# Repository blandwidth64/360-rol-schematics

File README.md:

# 360-rol-schematics
a collection of some ring of light revisions, scanned and digitized by me

i started the project in feb 2024 as my excuse to finally learn kicad
PLEASE PROOFREAD MY WORK BEFORE USING ANYTHING PLEASE PLEASE PRETTY PLEASE

along the way im doing my best to annotate all the traces i could competently identify, and for some traces im just guessing.

i will upload the work in order of whenever i am finished or whenever i think its good enough to go out.

thanks to drtrinity.

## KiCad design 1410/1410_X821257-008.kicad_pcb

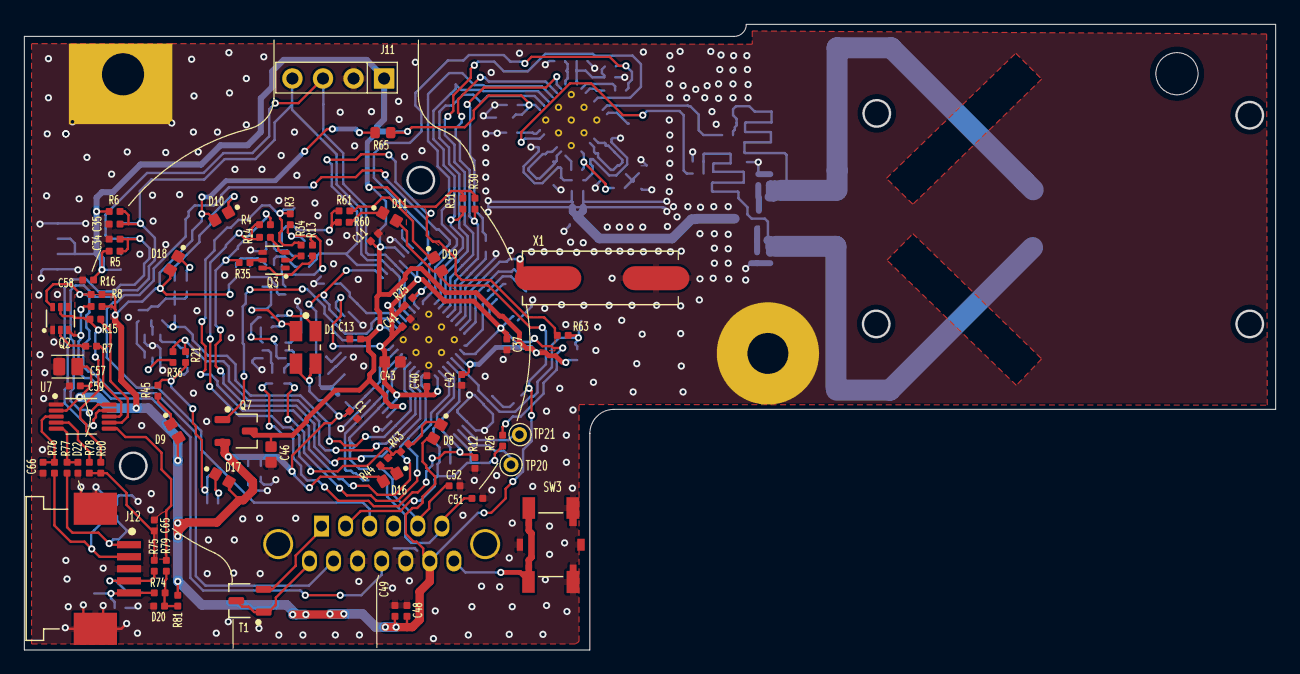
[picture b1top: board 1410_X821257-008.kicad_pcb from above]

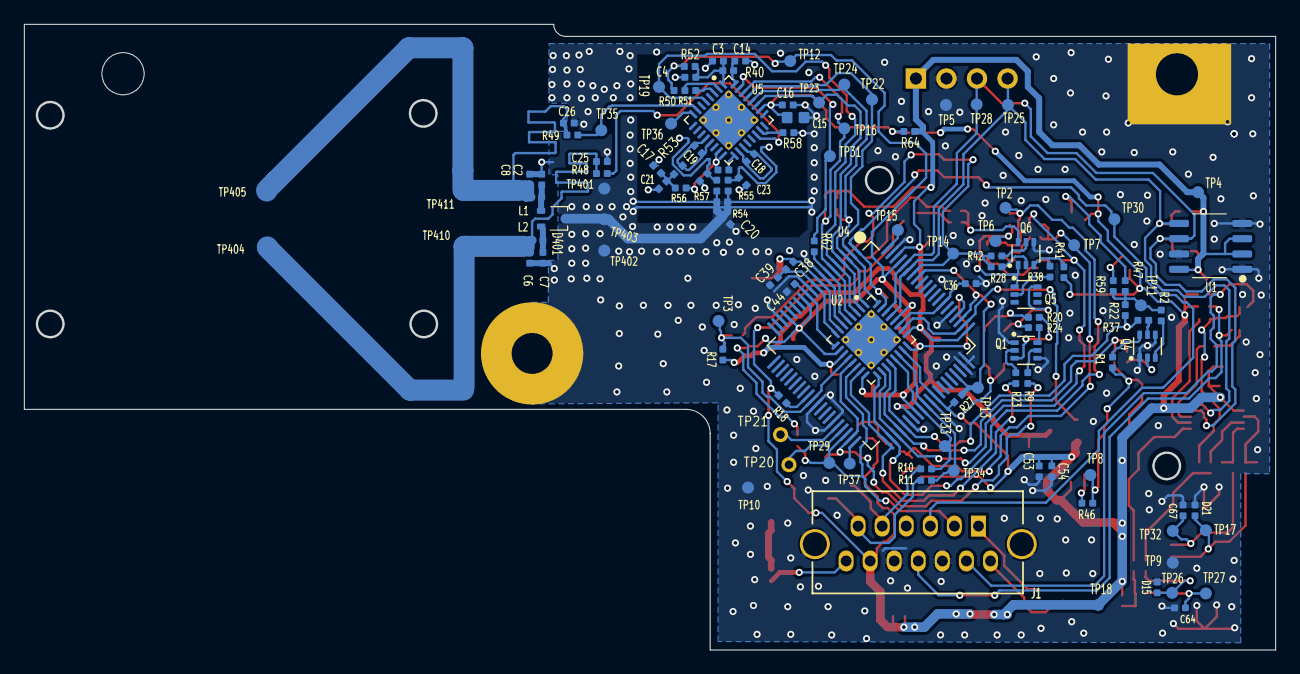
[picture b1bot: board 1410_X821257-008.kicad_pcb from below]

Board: 2 copper layers, 104.0 x 52.0 mm, 192 parts (119 on the bottom side), 64 nets.

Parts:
C1: 1 UF; C_0402_1005Metric
C2, C4, C6, C7, C8, C13, C16, C18, C19, C20, C21, C23, C25, C26, C34, C35, C51, C52, C64, C67: idk; C_0402_1005Metric
C3, C11, C14, C37, C40, C41, C42, C44, C48, C53, C58: 0.1 UF; C_0402_1005Metric
C15: C_0603_1608Metric
C17: 0.022 UF; C_0402_1005Metric
C36: 0.22 UF; C_0402_1005Metric
C38, C39: 27 pF; C_0402_1005Metric
C43, C46: 2.5 UF; C_0603_1608Metric
C49, C54: 2200 PF; C_0402_1005Metric
C57: 10 UF; C_0805_2012Metric
C59: 0.01 UF; C_0402_1005Metric
C65, C66: 62 PF; C_0402_1005Metric
D1: LED_Avago_PLCC4_3.2x2.8mm_CW
D8, D9, D10, D11, D16, D17, D18, D19: LED_0603_1608Metric
D15, D20, D21, D22: D_0402_1005Metric
D401: SOT-523
J1: BORONFPM
J11: PinHeader_1x04_P2.54mm_Vertical
J12: TE_84953-5_1x05-1MP_P1.0mm_Horizontal
L1, L2: L_0402_1005Metric
Q1, Q2, Q3, Q5, Q6: SOT-363_SC-70-6
Q4: NC; SOT-363_SC-70-6
Q7: SOT-23-3
R1, R2, R5, R13, R14, R27, R34, R35, R36, R37, R51, R52, R80, R81: NC; R_0402_1005Metric
R3, R4, R21, R22, R50, R53, R54, R55, R57, R62, R63, R78, R79: 0; R_0402_1005Metric
R6: 1500; R_0402_1005Metric
R7, R8, R15, R16, R25, R26, R40, R42: 10000; R_0402_1005Metric
R9, R17, R23, R28, R30, R31, R38, R41: 1000; R_0402_1005Metric
R10, R11: 22; R_0402_1005Metric
R12: 7.5; R_0402_1005Metric
R18, R56: 47; R_0402_1005Metric
R20: 190; R_0402_1005Metric
R24: 160; R_0402_1005Metric
R43, R44, R45, R46, R47, R59, R60, R61: 30; R_0402_1005Metric
R48, R49: 387; R_0402_1005Metric
R58, R64: 56; R_0402_1005Metric
R65: 2.2; R_0603_1608Metric
R74, R75, R76, R77: 100; R_0402_1005Metric
SW3: SW_Push_1P1T_XKB_TS-1187A
T1: SOT-23-3
TP2, TP3, TP4, TP5, TP6, TP7, TP8, TP9, TP10, TP11, TP12, TP13, TP14, TP15, TP16, TP17, TP18, TP19, TP22, TP23, TP24, TP25, TP26, TP27, TP28, TP29, TP30, TP31, TP32, TP33, TP34, TP35, TP36, TP37, TP401, TP402, TP403, TP404, TP405, TP410, TP411: TestPoint_Pad_D1.0mm
TP20, TP21: TestPoint_THTPad_D1.5mm_Drill0.7mm
U1: ST 24C04RP; SOP-8_3.9x4.9mm_P1.27mm
U2, U5: Microsoft X851186002; LFCSP-32-1EP_5x5mm_P0.5mm_EP3.6x3.6mm_ThermalVias
U4: U4; LQFP-80_12x12mm_P0.5mm
U7: MSOP-10_3x3mm_P0.5mm
UNPOPULATED: NC; R_0402_1005Metric
X1: 12MHz; Crystal_SMD_HC49-SD
unmarkedcap: idk; C_0402_1005Metric

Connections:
ANT_01: C8.1, C26.1, L1.1, R49.1, TP405.1, TP411.1
ANT_01_R1: R49.2, TP35.1, U5.7
ANT_02: C6.2, C25.1, L2.1, R48.1, TP404.1, TP410.1
ANT_02_R1: R48.2, U5.22
BINDSW_N: J1.13, SW3.2
BORONFPMPORT_DN: C52.2, J1.5, R10.2
BORONFPMPORT_DN_R: R10.1, TP33.1, U2.21, U4.49
BORONFPMPORT_DP: C51.2, J1.6, R11.2
BORONFPMPORT_DP_R: R11.1, TP34.1, U2.22, U4.50
BORONFPM_CLK: J1.3, R25.1, TP30.1, U2.31, U4.1
BORONFPM_DATA: J1.2, R26.2, TP29.1, U2.14, U4.38
BORONFPM_DATA_R: C37.1, C40.2, C41.2, C43.2, R25.2, R26.1, R50.1, R52.1, TP12.1, U2.10, U2.16, U2.24, U2.28, U4.13, U4.17, U4.48, U4.64, U4.77
BRD_TEMP_N: J1.7, T1.1, T1.3
BRD_TEMP_P: J1.1, T1.2
CPU_INTERCONN_01: R31.2, TP24.1, U2.1, U4.3, U5.28
CPU_INTERCONN_02: TP23.1, U2.2, U4.4, U5.27
CPU_INTERCONN_03: TP19.1, U2.3, U4.5, U5.5
CPU_INTERCONN_04: R30.2, TP16.1, U2.4, U4.6, U5.30
CPU_INTERCONN_05: R62.1, U2.5, U4.7
CPU_INTERCONN_05_0R: R62.2, TP31.1, U5.31
CPU_INTERCONN_06: TP22.1, U2.32, U4.2, U5.29
EJECTSW_N: J1.10, Q2.3, R8.2
FACEPL_EJECTSW_CIN: R78.1, U7.4
FACEPL_EJECTSW_CIN_0R: C65.2, R75.1, R78.2, R80.2
FACEPL_EJECTSW_CIN_R: D15.1, J12.4, R75.2, TP26.1
FACEPL_EJECTSW_EXC: R79.1, U7.6
FACEPL_EJECTSW_EXC_0R: D20.1, R74.1, R79.2, R81.2
FACEPL_EJECTSW_EXC_R: C64.1, J12.5, R74.2, TP27.1
FACEPL_EJECTSW_TRIG: R15.1, U7.7
FACEPL_PWRSW_CIN: C66.1, R76.1, U7.3
FACEPL_PWRSW_CIN_R: D21.1, J12.2, R76.2, TP17.1
FACEPL_PWRSW_EXC: D22.1, R77.1, U7.5
FACEPL_PWRSW_EXC_R: C67.2, J12.1, R77.2, TP32.1
FACEPL_PWRSW_TRIG: R7.1, U7.8
GND: C1.1, C2.2, C3.1, C4.1, C6.1, C7.1, C8.2, C11.1, C13.2, C14.2, C15.2, C16.2, C17.1, C20.1, C20.2, C21.1, C23.1, C23.2, C25.2, C26.2, C34.2, C35.2, C36.2, C37.2, C39.1, C40.1, C41.1, C42.2, C43.1, C44.1, C46.2, C48.1, C49.1, C51.1, C52.1, C53.1, C54.1, C57.1, C58.2, C59.2, C64.2, C65.1, C66.2, C67.1, D15.2, D20.2, D21.2, D22.2, D401.3, J1.9, J1.11, J1.14, J1.15, J11.2, J12.3, J12.MP, Q1.1, Q1.4, Q2.1, Q2.4, Q3.1, Q3.4, Q4.1, Q4.4, Q6.4, R12.2, R51.2, R54.1, R54.2, R55.1, R55.2, R57.1, R57.2, R58.2, SW3.1, TP5.1, TP9.1, TP10.1, TP401.1, TP402.1, TP403.1, U1.1, U1.4, U1.7, U2.6, U2.33, U4.8, U4.11, U4.18, U4.31, U4.35, U4.46, U4.51, U4.59, U4.60, U4.65, U4.79, U5.3, U5.6, U5.11, U5.14, U5.20, U5.33, U7.1, X1.2, unmarkedcap.1, unmarkedcap.2
I2C_SCL: C34.1, J11.3, R5.1, TP28.1, U1.6, U2.30, U4.76, U7.9
I2C_SDA: C35.1, J11.4, R6.1, TP25.1, U1.5, U2.29, U4.75, U7.10
LED_MAIN_GRN_EN: D1.4, Q5.6, R24.1
LED_MAIN_RED_EN: Q1.3, R20.2
LED_MAIN_RED_EN_R: D1.1, R20.1
LED_PL1_EN: R3.1, R34.1, TP2.1, U2.17, U4.42
LED_PL1_EN_0R: Q5.1, Q6.1, R3.2, R13.1, TP6.1
LED_PL1_EN_R1: D19.1, R61.1
LED_PL1_EN_R2: D11.1, R60.1
LED_PL1_EN_T: Q6.6, R60.2, R61.2
LED_PL2_EN: R4.1, R35.2, U2.18, U4.43
LED_PL2_EN_0R: R4.2, R14.2, R43.2, R44.1, TP7.1
LED_PL2_EN_R1: D8.1, R43.1
LED_PL2_EN_R2: D16.1, R44.2
LED_PL3_EN: R21.1, R36.1, U2.19, U4.44
LED_PL3_EN_0R: R1.1, R21.2, R45.1, R46.1, TP8.1
LED_PL3_EN_R1: D9.1, R45.2
LED_PL3_EN_R2: D17.1, R46.2
LED_PL4_EN: R22.1, R37.1, U2.20, U4.45
LED_PL4_EN_0R: R2.2, R22.2, R47.1, R59.1, TP11.1
LED_PL4_EN_R1: D10.1, R47.2
LED_PL4_EN_R2: D18.1, R59.2
PWRSW_N: J1.8, Q2.6, R16.2
SMD_XTAL: C38.2, U2.7, U4.9, X1.1
SMD_XTAL_C: C38.1, C39.2, U2.8, U4.10
V_2P0: C11.2, C13.1, C42.1, C46.1, C58.1, J11.1, Q7.3, R5.2, R6.2, R17.1, R30.1, R31.1, R64.2, TP4.1, U1.2, U1.3, U1.8, U2.11, U2.25, U4.47, U4.61, U4.78
V_2P7: Q7.1, U2.26, U4.62
V_3P3: C1.2, C48.2, C49.2, C53.2, C54.2, C57.2, C59.1, D1.2, D1.3, D8.2, D9.2, D10.2, D11.2, D16.2, D17.2, D18.2, D19.2, J1.12, Q7.2, R8.1, R16.1, R18.2, R27.2, R41.1, R65.1, R81.1, TP18.1, U2.23, U4.52, U7.2
V_3P3_R2P2: C15.1, C16.1, R64.1, R65.2, U5.26

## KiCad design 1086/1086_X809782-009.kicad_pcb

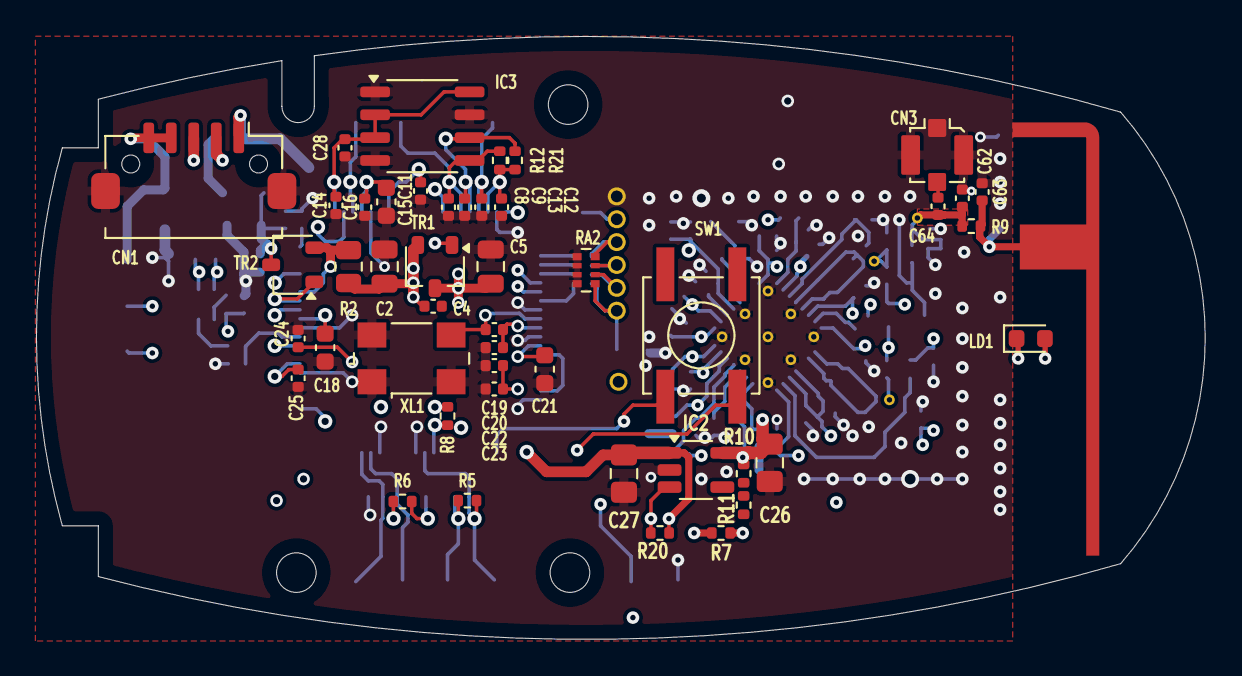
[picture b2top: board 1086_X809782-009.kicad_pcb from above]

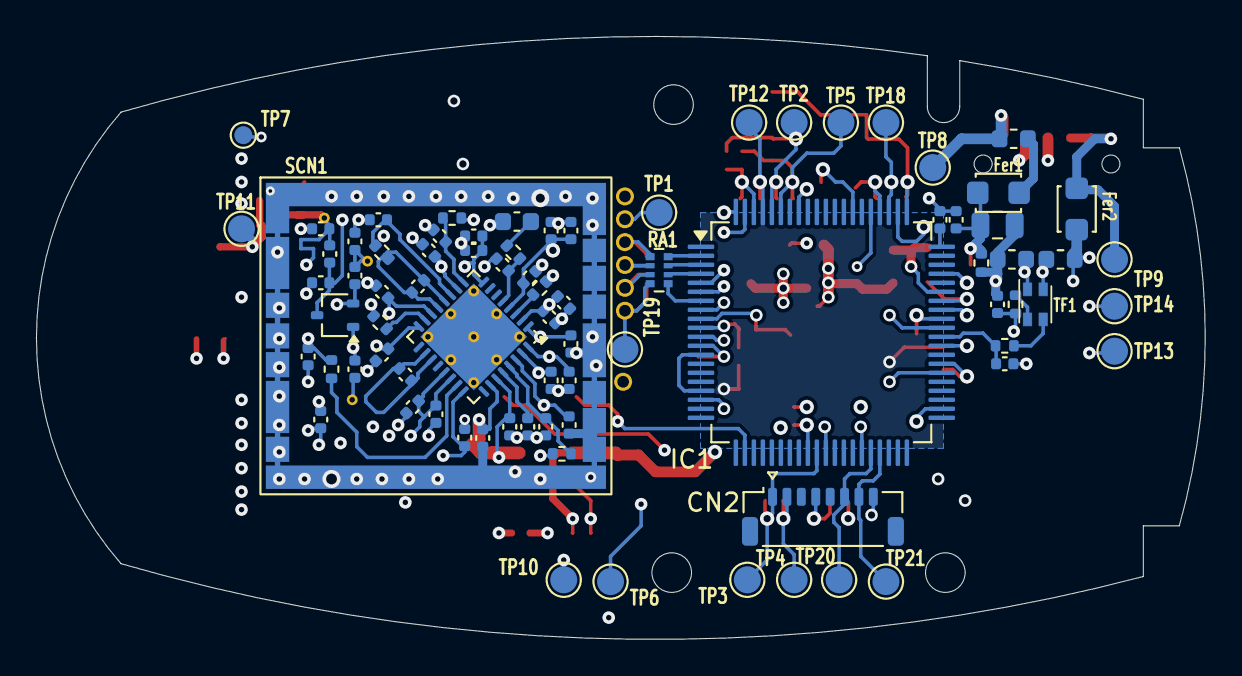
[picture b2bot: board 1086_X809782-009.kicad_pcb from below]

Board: 4 copper layers, 64.9 x 33.5 mm, 102 parts (56 on the bottom side), 41 nets.

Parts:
C1, C2: 10 UF; C_0805_2012Metric
C3, C4, C12, C13, C14, C16, C22, C23, C24, C25, C28, C30, C31, C47: 0.1 UF; C_0402_1005Metric
C5: 2.2 UF; C_0805_2012Metric
C6, C7: 10 PF; C_0402_1005Metric
C8, C9, C63, C64: NC; C_0402_1005Metric
C10, C17: 1000 PF; C_0402_1005Metric
C11: 0.22 UF; C_0402_1005Metric
C15, C18, C21: 1 UF; C_0603_1608Metric
C19, C20: ~2.7 PF; C_0402_1005Metric
C26, C27: NC; C_0805_2012Metric_Pad1.18x1.45mm_HandSolder
C36, C50, C51: 1100 PF; C_0402_1005Metric
C38: ~2.2 PF; C_0402_1005Metric
C39, C40: ~6 PF; C_0402_1005Metric
C41, C42, C53: ~1 PF; C_0402_1005Metric
C52: ~10 PF; C_0402_1005Metric
C61: 0.022 UF; C_0402_1005Metric
C62: 2.2 PF; C_0402_1005Metric
CN1: Molex_CLIK-Mate_502382-0570_1x05-1MP_P1.25mm_Vert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; Molex_CLIK-Mate_502382-0570_1x05-1MP_P1.25mm_Vertical
CN2: Hirose_DF52-8S-0.8H_1x08-1MP_P0.80mm_Horizontal
CN3: U.FL_Molex_MCRF_73412-0110_Vertical
D4: SOT-323_SC-70
F1: Fuse_0603_1608Metric
Fer1, Fer2: L_Walsin_WLFM201609x
IC1: LQFP-80_12x12mm_P0.5mm
IC2: SOT-23-5_HandSoldering
IC3: SOP-8_3.9x4.9mm_P1.27mm
LD1: LED_0603_1608Metric
R1, R3: 33 OHM; R_0402_1005Metric
R2: 0.27 OHM; R_0805_2012Metric
R4: 100 KOHM; R_0402_1005Metric
R5: 1 KOHM; R_0402_1005Metric
R6, R8, R9, R10, R11, R20, R21: NC; R_0402_1005Metric
R7: 0 OHM; R_0402_1005Metric
R12: 4.7 KOHM; R_0402_1005Metric
R14: 180 OHM; R_0402_1005Metric
R15: 390 OHM; R_0402_1005Metric
R17: 12 KOHM; R_0402_1005Metric
R19: 18 OHM; R_0402_1005Metric
RA1: 100 OHM; R_Array_Convex_4x0402
RA2: NC; R_Array_Convex_4x0402
SCN1: XRFShield
SW1: SW_SPST_PTS645
TF1: L_CommonModeChoke_Coilcraft_0805USB
TP1, TP2, TP3, TP4, TP5, TP6, TP8, TP9, TP10, TP11, TP12, TP13, TP14, TP18, TP19, TP20, TP21: TestPoint_Pad_D1.5mm
TP7: TestPoint_Pad_D1.0mm
TR1: BC807-40; SOT-23W
TR2: BC817-40; SOT-23W
VR1, VR2: L_0603_1608Metric
XL1: Crystal_SMD_0603-4Pin_6.0x3.5mm

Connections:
ANT_01: C63.1, R9.2, TP11.1
GND: C1.2, C2.2, C3.2, C4.1, C5.2, C6.2, C7.1, C8.2, C9.2, C10.2, C11.2, C12.2, C13.2, C14.2, C15.2, C16.2, C17.2, C18.2, C20.2, C21.2, C22.2, C23.2, C24.2, C25.2, C26.2, C27.1, C28.2, C30.1, C31.1, C36.1, C38.2, C39.1, C40.1, C42.1, C42.2, C47.2, C50.1, C51.1, C52.2, C53.1, C53.2, C61.2, C62.1, C62.2, C63.2, C64.1, CN1.MP, CN2.8, CN3.2, D4.3, Fer2.2, IC1.8, IC1.11, IC1.18, IC1.31, IC1.35, IC1.46, IC1.51, IC1.65, IC1.79, IC2.2, IC3.1, IC3.4, IC3.7, R4.1, R9.1, RA2.1, RA2.2, RA2.3, RA2.4, SCN1.1, TP7.1, TP10.1, VR1.1, VR2.2, XL1.1, XL1.2, XL1.4
HEADER_04: CN2.4, R6.2
HEADER_06: CN2.6, IC1.36, TP20.1
HEADER_07: CN2.7, IC1.37, TP21.1
I2C_SCL: C9.1, IC1.76, IC3.6, R21.1, TP2.1
I2C_SDA: C8.1, IC1.75, IC3.5, R12.1, TP5.1
INTER_01: IC1.2, RA1.8
INTER_01_R: RA1.1, RA2.8
INTER_02: IC1.3, RA1.7
INTER_02_R: RA1.2, RA2.7
INTER_03: IC1.4, RA1.6
INTER_03_R: RA1.3, RA2.6
INTER_04: IC1.5, TP1.1
INTER_06: IC1.7, RA1.5
INTER_06_R: R14.1, RA1.4, RA2.5, TP19.1
LAMPREY_NTX: CN2.1, IC1.30, R5.2, TP3.1
LED_EN: IC1.42, LD1.1, TP6.1
MCU_DECOUP: C13.1, C15.1, C16.1, C22.1, C23.1, C24.1, IC1.13, IC1.17, IC1.48, IC1.64, IC1.77, TP12.1
NC: IC1.1, IC1.14, IC1.15, IC1.16, IC1.19, IC1.20, IC1.21, IC1.23, IC1.24, IC1.25, IC1.26, IC1.27, IC1.28, IC1.32, IC1.33, IC1.34, IC1.38, IC1.39, IC1.40, IC1.41, IC1.43, IC1.44, IC1.45, IC1.56, IC1.58, IC1.59, IC1.66, IC1.68, IC1.69, IC1.70, IC1.71, IC1.72, IC1.74
SMD_XTAL: C19.1, IC1.9, XL1.3
SMD_XTAL_C: C19.2, C20.1, IC1.10
SYNCBTN: IC1.22, SW1.1
SYNCBTN_DEBOUNCE: C18.1, IC1.52, SW1.2
USB_5V_C: C1.1, C3.1, Fer1.2, IC1.53, R4.2, R6.1, TR2.3
USB_DN: CN1.2, TF1.1, TP13.1, VR1.2
USB_DN_I: R1.2, TF1.2
USB_DN_R: C6.1, IC1.49, R1.1
USB_DP: CN1.3, TF1.4, TP14.1, VR2.1
USB_DP_I: R3.2, TF1.3
USB_DP_R: C7.2, IC1.50, R3.1
USB_GND: CN1.4, CN1.5, Fer2.1, TP9.1
USB_VBUS: CN1.1, F1.1, TP8.1
USB_VBUS_F: F1.2, Fer1.1
V_2P0_TBASE: IC1.62, TR1.1
V_3P3: C2.1, C4.2, C27.2, IC1.57, IC1.63, IC1.73, IC2.1, LD1.2, R2.1, R8.1, R20.2, TP18.1, TR1.2
V_3P3_LOW: C5.1, C12.1, C14.1, C25.1, C28.1, CN2.2, IC1.47, IC1.61, IC1.78, IC3.2, IC3.3, IC3.8, R5.1, R7.1, R12.2, R21.2, TP4.1, TR1.3
V_3P3_LOW_0R: C10.1, C26.1, C30.2, C31.2, C36.2, C47.1, C50.2, C51.2, C52.1, IC2.5, R7.2, R10.1
V_3P3_T: IC1.55, R2.2, TR2.2
V_3P3_TBASE: IC1.54, TR2.1
maybe_v3_r: IC1.29, R8.2

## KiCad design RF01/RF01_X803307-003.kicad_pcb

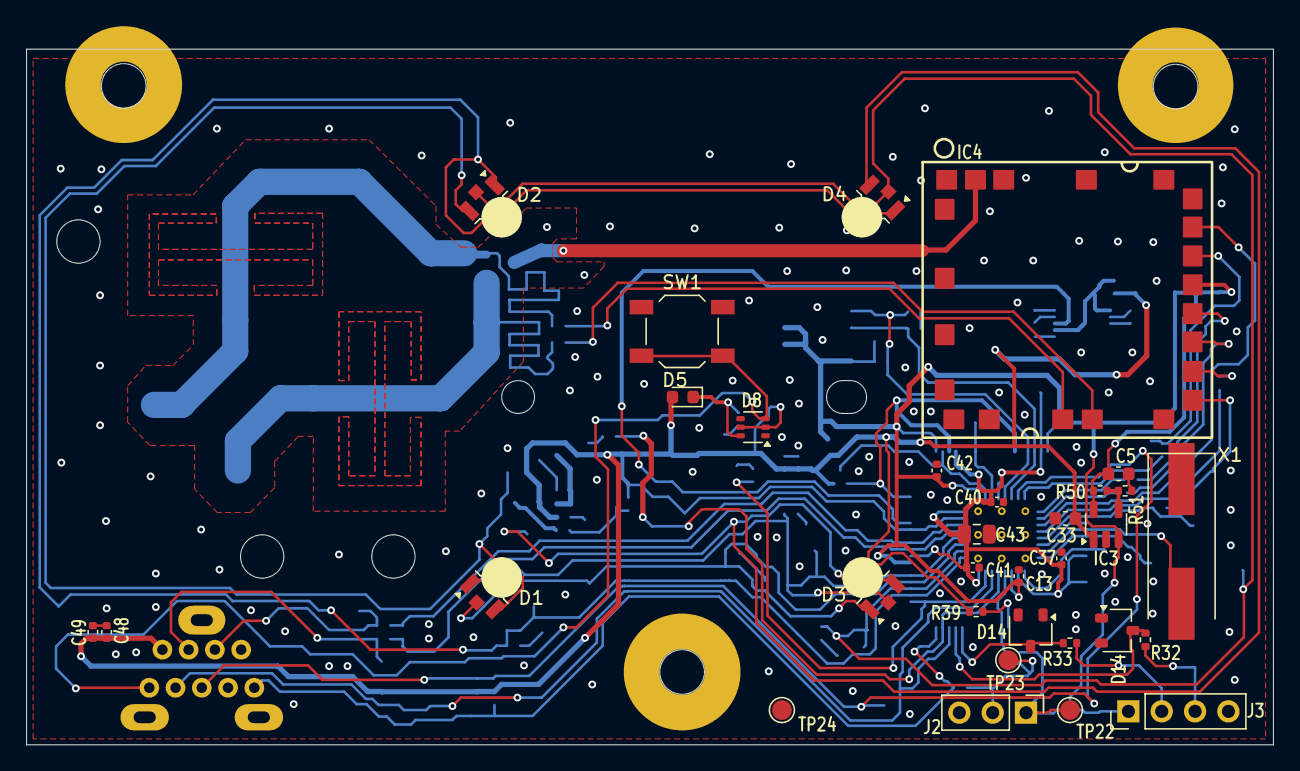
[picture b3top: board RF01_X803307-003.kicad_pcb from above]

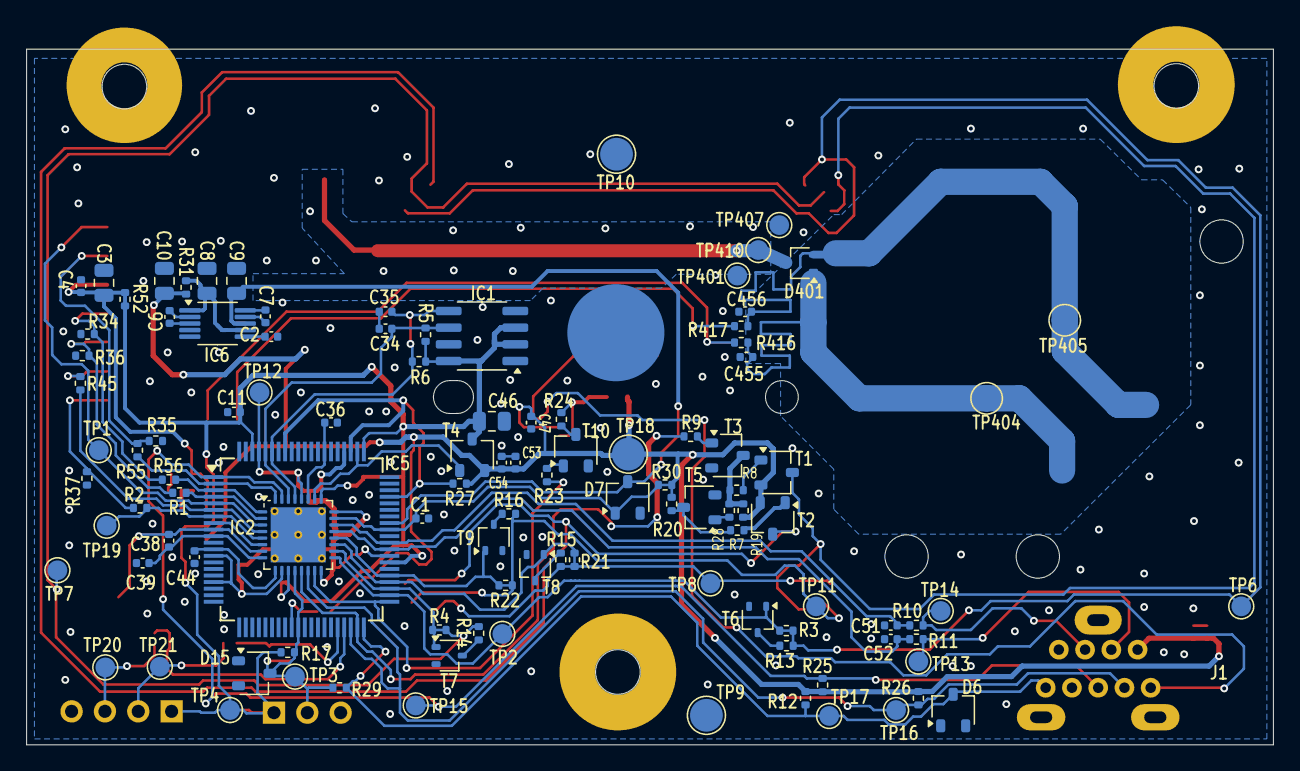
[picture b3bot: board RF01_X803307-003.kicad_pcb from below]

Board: 2 copper layers, 95.0 x 53.0 mm, 144 parts (108 on the bottom side), 35 nets.

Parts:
C1, C2, C4, C6, C7, C11, C34, C35, C36, C38, C42, C44, C47, C53, C54, C455, C456: C_0402_1005Metric
C3, C8, C9, C10: C_0805_2012Metric
C5, C33: NC; C_0603_1608Metric
C13, C37, C40, C41: 0.1 UF; C_0402_1005Metric
C39: 27 PF; C_0402_1005Metric
C43, C46: 2.5 UF; C_0805_2012Metric
C48, C49: NC; C_0402_1005Metric
C51, C52: 36 UF; C_0402_1005Metric
D1, D2, D3, D4: LED_LiteOn_LTST-S326
D5: LED_0603_1608Metric
D6, D7, D14, D14#2, D15: SOT-23W
D8: SOT-363_SC-70-6
D401: SOT-323_SC-70
IC1: SOP-8_3.76x4.96mm_P1.27mm
IC2: LFCSP-32-1EP_5x5mm_P0.5mm_EP3.6x3.6mm_ThermalVias
IC3: SOT-23-5
IC4: RF_Subboard_Host
IC5: TQFP-80_12x12mm_P0.5mm
IC6: MSOP-10_3x3mm_P0.5mm
J1: Argon_Conn
J2: PinHeader_1x03_P2.54mm_Vertical
J3: PinHeader_1x04_P2.54mm_Vertical
Mouning1: MountingHole_3.5mm_Pad
Mounting2, Mounting3: MountingHole_3.5mm_Pad
Mounting4: TestPoint_Pad_D4.0mm
R1, R56: 100 OHM; R_0402_1005Metric
R2, R4, R5, R6, R7, R8, R9, R12, R14, R16, R17, R19, R20, R25, R28, R29, R30, R31, R33, R34, R35, R36, R37, R45, R52, R55, R416, R417: R_0402_1005Metric
R3, R13, R15, R21, R22, R26, R27, R32, R39, R50, R51: NC; R_0402_1005Metric
R10, R11: 22 OHM; R_0402_1005Metric
R23: 1 KOHM; R_0402_1005Metric
R24: 238 OHM; R_0402_1005Metric
SW1: SW_Push_1P1T_XKB_TS-1187A
T1, T2, T3, T4, T5: SOT-23W
T6, T7, T8, T9: SOT-323_SC-70
T10: PMBT3094; SOT-23W
TP1, TP2, TP3, TP4, TP6, TP7, TP8, TP11, TP12, TP13, TP14, TP15, TP16, TP17, TP19, TP20, TP21, TP22, TP23, TP24, TP401, TP407, TP410: TestPoint_Pad_D1.5mm
TP9, TP10, TP18: TestPoint_Pad_D2.5mm
TP404, TP405: TestPoint_Pad_D2.0mm
X1: Crystal_SMD_HC49-SD

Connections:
ANT_01: C456.1, D401.2, R417.1, TP405.1
ANT_02: C455.1, D401.1, R416.1, TP404.1
C_CLK: IC2.31, IC5.1, J1.7, R25.2, TP15.1
C_DATA: IC2.14, IC5.38, J1.6, R26.1, TP16.1
C_LAMPREY_NTX: D6.3, IC5.40, J1.9, R12.1, R29.1, TP17.1
C_LAMPREY_NTX_R: D15.3, IC2.12, IC5.30, J2.2, R17.1, R29.2, TP3.1, TP23.1
GND: C1.1, C2.2, C3.1, C4.1, C5.2, C8.1, C9.1, C10.1, C11.2, C13.2, C33.1, C34.2, C35.2, C36.1, C37.2, C39.2, C40.2, C41.2, C42.2, C43.2, C44.2, C46.1, C47.2, C48.2, C49.2, C51.2, C52.2, C53.1, C54.1, C455.2, C456.2, D6.1, D8.1, D8.4, D14.1, D14#2.1, D15.1, IC1.1, IC1.4, IC1.7, IC2.6, IC2.33, IC3.2, IC4.1, IC4.2, IC4.3, IC4.4, IC4.5, IC4.6, IC4.9, IC4.17, IC4.18, IC4.19, IC4.20, IC4.22, IC5.8, IC5.11, IC5.18, IC5.31, IC5.35, IC5.46, IC5.65, IC5.79, IC6.4, IC6.5, J1.4, J1.8, J1.MP, J2.3, J3.4, Mounting3.1, Mounting4.1, R34.2, R35.1, R36.2, R37.2, R51.2, SW1.1, T3.2, T5.2, T6.2, T7.2, T8.2, T9.2, T10.2, TP9.1, TP10.1, TP24.1, TP401.1, TP407.1, X1.1
I2C_SCL: C34.1, IC1.6, IC2.30, IC5.76, R5.2
I2C_SDA: C35.1, IC1.5, IC2.29, IC5.75, R6.2
INTER01: IC2.1, IC5.3, R56.1
INTER01_R: IC4.13, R34.1, R56.2
INTER02_R: IC4.12, R1.2, R36.1
INTER03: IC2.3, IC4.16, IC5.5, TP1.1
INTER04: IC2.4, IC5.6, R45.1
INTER04_R: IC4.11, R45.2
INTER05: IC2.5, IC5.7, R2.1, TP19.1
INTER05_R: IC4.10, R2.2, R37.1
INTER06: IC2.32, IC5.2, R55.2
INTER06_R: IC4.15, R35.2, R55.1
INTER_02: IC2.2, IC5.4, R1.1
MCU_DECOUP: C37.1, C40.1, C41.1, C43.1, IC2.10, IC2.16, IC2.24, IC2.28, IC5.13, IC5.17, IC5.48, IC5.64, IC5.77, TP12.1
OTHER-VOLTAGE: C3.2, C4.2, C5.1, C11.1, C13.1, C42.1, C46.2, IC1.2, IC1.3, IC1.8, IC2.11, IC2.25, IC3.3, IC3.5, IC4.14, IC5.47, IC5.61, IC5.78, J2.1, J3.1, R5.1, R6.1, R17.2, R50.1, R52.1, R52.2, T4.3, TP4.1, TP22.1
PWRSW_N: D8.3, J1.5, SW1.2
TEMP_HEADER1_2: J3.2, R33.2, TP21.1
TEMP_HEADER1_3: J3.3, R32.1, TP20.1
TEMP_HEADER1_3R: D14#2.3, IC5.37, R32.2
USB_DN: J1.2, R11.1, TP13.1
USB_DN_R1: C52.1, IC2.21, IC5.49, R11.2
USB_DP: J1.3, R10.1, TP14.1
USB_DP_R1: C51.1, IC2.22, IC5.50, R10.2
V_3P3: C1.2, C10.2, C33.2, C47.1, C48.1, C49.1, C53.2, C54.2, D5.2, D7.1, D8.2, D8.5, IC2.23, IC3.1, IC5.52, J1.1, R12.2, R19.1, R20.1, R25.1, R26.2, R27.1, R30.1, R30.2, R31.1, R39.1, T1.2, T2.2, T4.2, TP18.1
XTAL_IN: C38.1, IC2.7, IC5.9, X1.2
XTAL_IN_C: C38.2, C39.1, IC2.8, IC5.10
nonet: D401.3, IC4.21, TP410.1
placeholder: C9.2, D7.3, IC5.53, IC6.8

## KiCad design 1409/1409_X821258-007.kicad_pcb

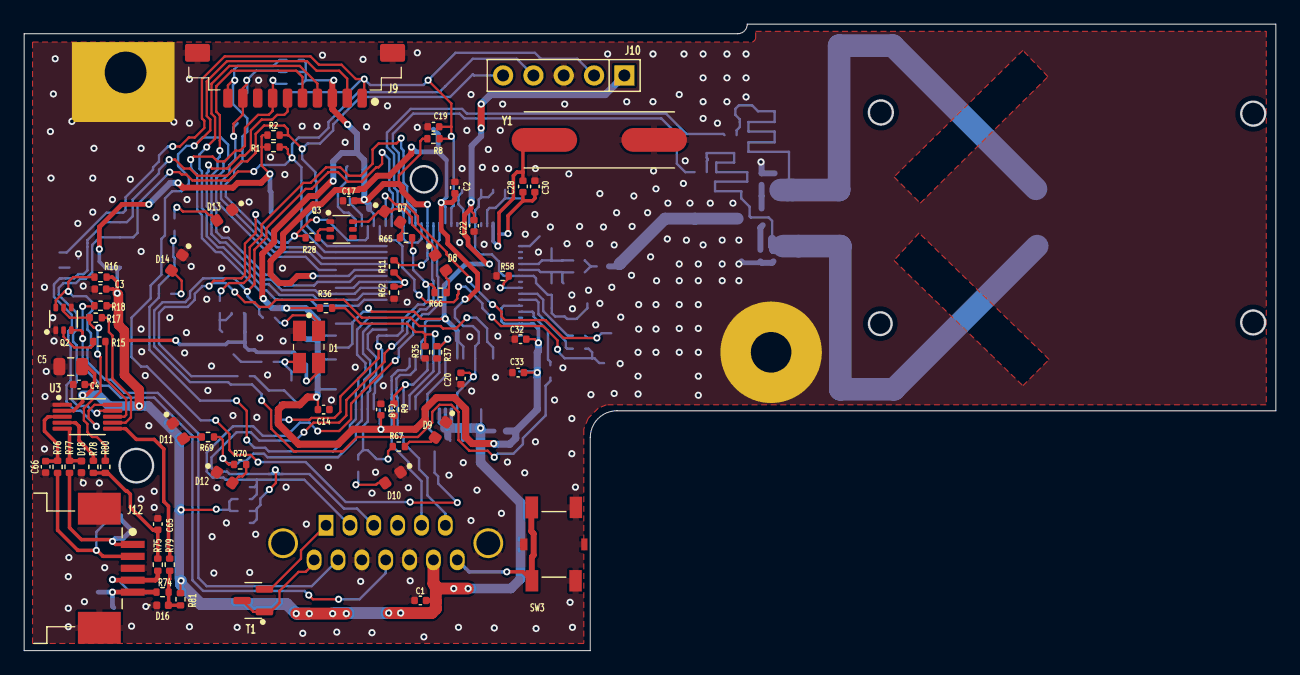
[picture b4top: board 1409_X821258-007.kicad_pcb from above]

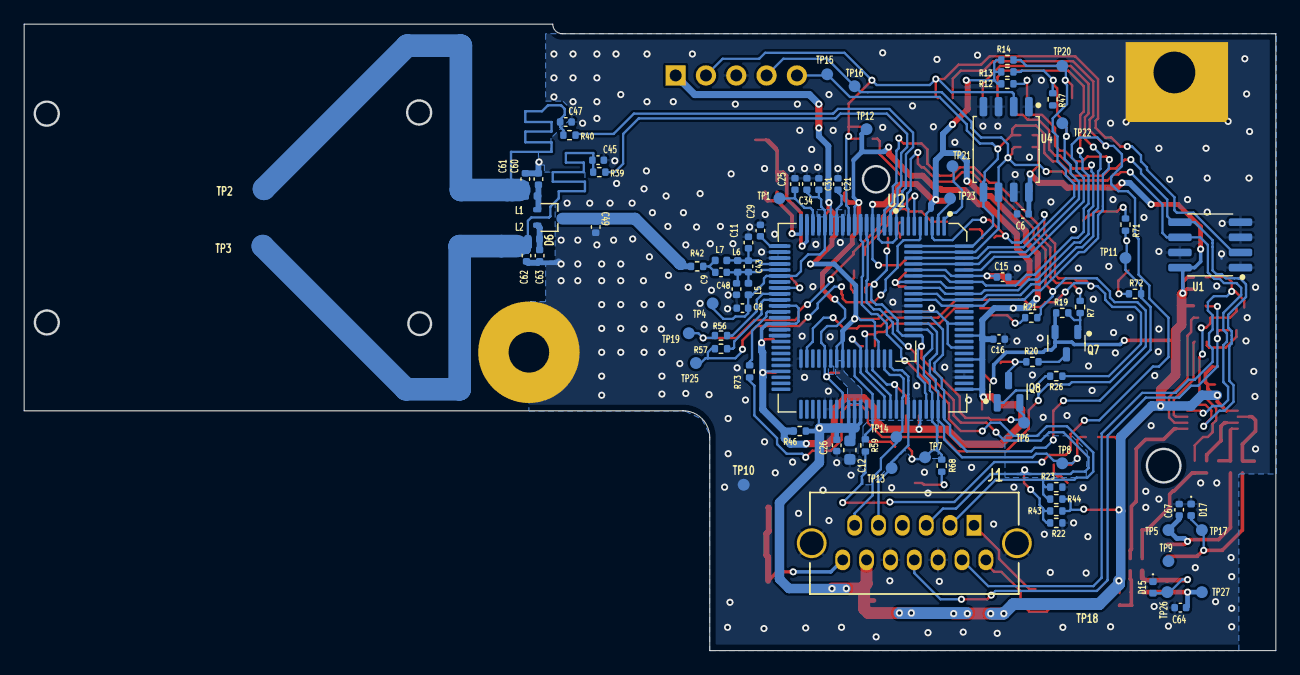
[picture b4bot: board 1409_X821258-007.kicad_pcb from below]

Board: 2 copper layers, 104.9 x 52.5 mm, 154 parts (88 on the bottom side), 86 nets.

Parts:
C1, C4: 0.01 UF; C_0402_1005Metric
C2, C3, C8, C14, C17, C18, C19, C20, C21, C22, C25, C26, C29, C32, C33, C34: 0.1 UF; C_0402_1005Metric
C5: 10 UF; C_0805_2012Metric
C6, C15, C16, C45, C47, C64: C_0402_1005Metric
C9: ~1 PF; C_0402_1005Metric
C11, C43: ~2 PF; C_0402_1005Metric
C12: C_0603_1608Metric
C28: 22 PF; C_0402_1005Metric
C30: 16 PF; C_0402_1005Metric
C31: 100 PF; C_0402_1005Metric
C48, C49, C60, C63, C67: NC; C_0402_1005Metric
C61, C62: ~0.8 PF; C_0402_1005Metric
C65, C66: 62 PF; C_0402_1005Metric
D1: LED_RGB_Wuerth-PLCC4_3.2x2.8mm_150141M173100
D6: SOT-323_SC-70
D7, D8, D9, D10, D11, D12, D13, D14: LED_0603_1608Metric
D15, D17: D_0402_1005Metric
D16, D18: NC; D_0402_1005Metric
J1: Boron_Conn
J9: Molex_PicoBlade_53261-1071_1x10-1MP_P1.25mm_Horiz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; Molex_PicoBlade_53261-1071_1x10-1MP_P1.25mm_Horizontal
J10: PinHeader_1x05_P2.54mm_Vertical
J12: TE_84953-5_1x05-1MP_P1.0mm_Horizontal
L1, L2, L5, L6, L7: L_0402_1005Metric
Q2, Q3: SOT-363_SC-70-6
Q7, Q8: PMBT3906; SOT-23
R1, R2: 1.5 KOHM; R_0402_1005Metric
R7, R26, R28: 1 KOHM; R_0402_1005Metric
R8: 47 KOHM; R_0402_1005Metric
R9, R11, R36, R47, R80, R81: NC; R_0402_1005Metric
R12, R13, R14, R15, R16, R17, R18, R19, R35, R37, R43, R44, R62: 10 KOHM; R_0402_1005Metric
R20: 160 OHM; R_0402_1005Metric
R21: 191 OHM; R_0402_1005Metric
R22, R23: 24.6 KOHM; R_0402_1005Metric
R39, R40: 390 OHM; R_0402_1005Metric
R42, R46, R56, R57, R58, R59, R73, R78, R79: 0 OHM; R_0402_1005Metric
R65, R66, R67, R68, R69, R70, R71, R72: 30 OHM; R_0402_1005Metric
R74, R75, R76, R77: 100 OHM; R_0402_1005Metric
SW3: SW_Push_1P1T_XKB_TS-1187A
T1: SOT-23
TP1, TP4, TP5, TP6, TP7, TP8, TP9, TP10, TP11, TP12, TP13, TP14, TP15, TP16, TP17, TP18, TP19, TP20, TP21, TP22, TP23, TP25, TP26, TP27: TestPoint_Pad_D1.0mm
TP2, TP3: TestPoint_Pad_D2.0mm
U1: SOP-8_3.76x4.96mm_P1.27mm
U2: LQFP-64_10x10mm_P0.5mm
U2_2: LQFP-100_14x14mm_P0.5mm
U3: MSOP-10_3x3mm_P0.5mm
U4: SOIC-8_5.3x5.3mm_P1.27mm
Y1: Crystal_SMD_HC49-SD

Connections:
ANT_01: C47.1, C61.1, L1.2, R40.1, TP2.1
ANT_01_L: C60.1, D6.1, L1.1
ANT_01_MATCHING: R40.2, U2.3, U2_2.9, U2_2.12
ANT_02: C45.1, C62.2, L2.2, R39.1, TP3.1
ANT_02_L: C63.2, D6.2, L2.1
ANT_02_MATCHING: R39.2, U2.1, U2_2.10
ANT_MAIN: C49.1, D6.3, R42.1
ANT_MAIN_C: C9.1, C43.1, C48.1, L5.2, L6.1, U2.21, U2_2.30
ANT_MAIN_L: C11.1, C43.2, L6.2, L7.1, U2.20, U2_2.29
ANT_MAIN_R: C9.2, L7.2, R42.2
BINDSW_N: J1.13, SW3.1
C_CLK: J1.3, R22.1, R43.1, U2.5, U2_2.14
C_DATA: J1.2, R23.1, R44.1, U2.6, U2_2.15
C_NTX: TP21.1, U2_2.1
FP_EJCSW_CIN: R78.2, U3.4
FP_EJCSW_CIN_0R: C65.1, R75.2, R78.1, R80.1
FP_EJCSW_CIN_R: D15.2, J12.4, R75.1, TP26.1
FP_EJCSW_EXC: R79.2, U3.6
FP_EJCSW_EXC_0R: D16.2, R74.2, R79.1, R81.1
FP_EJCSW_EXC_R: C64.2, J12.5, R74.1, TP27.1
FP_EJCSW_TRIG: R17.2, U3.7
FP_EJCSW_TRIG_R: Q2.5, R17.1, R80.2
FP_PWRSW_CIN: C66.1, R76.2, U3.3
FP_PWRSW_CIN_R: D17.2, J12.2, R76.1, TP17.1
FP_PWRSW_EXC: D18.2, R77.2, U3.5
FP_PWRSW_EXC_R: C67.1, J12.1, R77.1, TP5.1
FP_PWRSW_TRIG: R15.2, U3.8
FP_PWRSW_TRIG_R: Q2.2, R15.1
GND: C1.2, C2.2, C3.2, C4.2, C5.2, C6.1, C8.2, C11.2, C12.2, C14.2, C15.2, C16.2, C17.2, C18.2, C19.2, C20.2, C21.2, C22.2, C25.2, C26.1, C29.2, C30.2, C31.2, C32.2, C33.2, C34.2, C45.2, C47.2, C48.2, C49.2, C60.2, C61.2, C62.1, C63.1, C64.1, C65.2, C66.2, C67.2, D1.4, D9.1, D10.1, D11.1, D12.1, D13.1, D14.1, D15.1, D16.1, D17.1, D18.1, J1.9, J1.11, J1.MP, J9.8, J9.MP, J10.3, J12.3, J12.MP, Q2.1, Q2.4, Q3.1, R22.2, R23.2, R35.2, R37.2, R58.2, R62.2, SW3.2, SW3.MP, TP10.1, U1.1, U1.3, U1.4, U1.7, U2.9, U2.13, U2.18, U2.19, U2.33, U2.38, U2.54, U2_2.18, U2_2.22, U2_2.27, U2_2.28, U2_2.46, U2_2.55, U2_2.56, U2_2.57, U2_2.70, U2_2.78, U2_2.79, U3.1, U4.1, U4.3, U4.4, U4.7, Y1.2
GND_0R: R58.1, U2.24, U2_2.33
GND_R: R37.1, U2.43, U2_2.65
GND_R2: R35.1, R36.2, U2.44, U2_2.66
HEADER_02: J9.2, R59.1, U2_2.96
HEADER_02_0R: R59.2, U2.42, U2_2.63
HEADER_04: J9.4, U2.56, U2_2.91
HEADER_05: J9.5, U2.59, U2_2.94
HEADER_06: J9.6, U2.57, U2_2.92
HEADER_07: J9.7, R12.2, U2.55, U2_2.90
I2C_EN: C19.1, J9.1, J10.2, R8.2, U1.2, U2.8, U2_2.17, U4.2
I2C_SCL: J10.4, R1.2, TP16.1, U1.6, U2.63, U2_2.99, U3.9, U4.6
I2C_SDA: J10.5, R2.2, TP15.1, U1.5, U2.64, U2_2.100, U3.10, U4.5
LED_PL0_GRN: D1.2, Q8.3, R20.1
LED_PL0_GRN_EN: R7.2, U2.2, U2_2.11
LED_PL0_GRN_R: Q7.3, R20.2
LED_PL0_GRN_TBASE: Q7.1, R7.1, R19.2
LED_PL0_RED: D1.3, R21.1
LED_PL0_RED_0R: R73.2, U2.28, U2_2.37
LED_PL0_RED_R: R21.2, R73.1, U2_2.7
LED_PL1_01_R: D7.2, R65.1
LED_PL1_02_R: D8.2, R66.2
LED_PL1_EN: Q8.2, R65.2, R66.1, TP6.1, U2.49, U2_2.72
LED_PL1_TR: D7.1, D8.1, Q3.6
LED_PL2_01: D9.2, R67.2
LED_PL2_02: D10.2, R68.1
LED_PL2_EN: R67.1, R68.2, TP7.1, U2.50, U2_2.73
LED_PL3_01: D11.2, R69.1
LED_PL3_02: D12.2, R70.2
LED_PL3_EN: R69.2, R70.1, TP8.1, U2.51, U2_2.74
LED_PL4_01: D13.2, R71.2
LED_PL4_02: D14.2, R72.1
LED_PL4_EN: R71.1, R72.2, TP11.1, U2.52, U2_2.75
NC: U2.23, U2.29, U2.31, U2.32, U2.35, U2.36, U2.41, U2_2.32, U2_2.38, U2_2.40, U2_2.41, U2_2.42, U2_2.43, U2_2.44, U2_2.45, U2_2.48, U2_2.49, U2_2.50, U2_2.51, U2_2.52, U2_2.53, U2_2.62, U2_2.64, U2_2.77, U2_2.80, U2_2.82, U2_2.84, U2_2.86, U2_2.88, U2_2.89
ODD_EJCT: J1.10, Q2.3, R18.1
PWRSW_N: J1.8, Q2.6, R16.1, TP23.1, U2_2.2
S2B_01: R56.2, U2.25, U2_2.34
S2B_01_0R: R56.1, TP19.1, U2_2.6
S2B_02: R57.2, U2.26, U2_2.35
S2B_02_0R: R57.1, TP25.1, U2_2.5
SMD_XTAL: C28.2, U2.15, U2_2.24, Y1.1
SMD_XTAL_C: C28.1, C30.1, U2.16, U2_2.25
TEMP_N: J1.7, T1.1, T1.3
TEMP_P: J1.1, T1.2
UART_RX?: J9.9, R13.2, R47.2, TP22.1, U2.61, U2_2.97
UART_TX?: J9.10, R14.2, TP20.1, U2.62, U2_2.98
USB_DN: J1.5, TP13.1, U2.48, U2_2.69
USB_DP: J1.6, TP14.1, U2.47, U2_2.68
V_3P3: C1.1, C3.1, C4.1, C5.1, C6.2, C12.1, C22.1, C26.2, D1.1, J1.12, J10.1, Q7.2, R1.1, R2.1, R16.2, R18.2, R19.1, R43.2, R44.2, R46.2, R81.2, TP18.1, U1.8, U2.11, U2.39, U2.40, U2.46, U2.53, U2_2.20, U2_2.54, U2_2.59, U2_2.60, U2_2.61, U2_2.83, U2_2.87, U3.2, U4.8
V_3P3_0R: C14.1, C16.1, C17.1, C18.1, C32.1, C33.1, J9.3, R8.1, R9.1, R11.2, R12.1, R13.1, R14.1, R36.1, R46.1, U2.4, U2.27, U2.30, U2_2.4, U2_2.13, U2_2.36, U2_2.39, U2_2.47, U2_2.71, U2_2.76, U2_2.81, U2_2.85
V_3P3_ISO_NC: R9.2, U2.45, U2_2.67
V_3P3_NC: R11.1, R62.1, U2.58, U2_2.93
decouple_1: C2.1, C15.1, C20.1, TP12.1, U2.7, U2.37, U2.60, U2_2.16, U2_2.58, U2_2.95
decouple_2: C25.1, TP1.1, U2.14, U2_2.23
decouple_3: C29.1, U2.17, U2_2.26
decouple_4: C8.1, C31.1, C34.1, L5.1, TP4.1, U2.12, U2.22, U2_2.21, U2_2.31
decouple_5: C21.1, U2.10, U2_2.19
ledplaceholder: R26.2, R28.1, U2.34, U2_2.3
